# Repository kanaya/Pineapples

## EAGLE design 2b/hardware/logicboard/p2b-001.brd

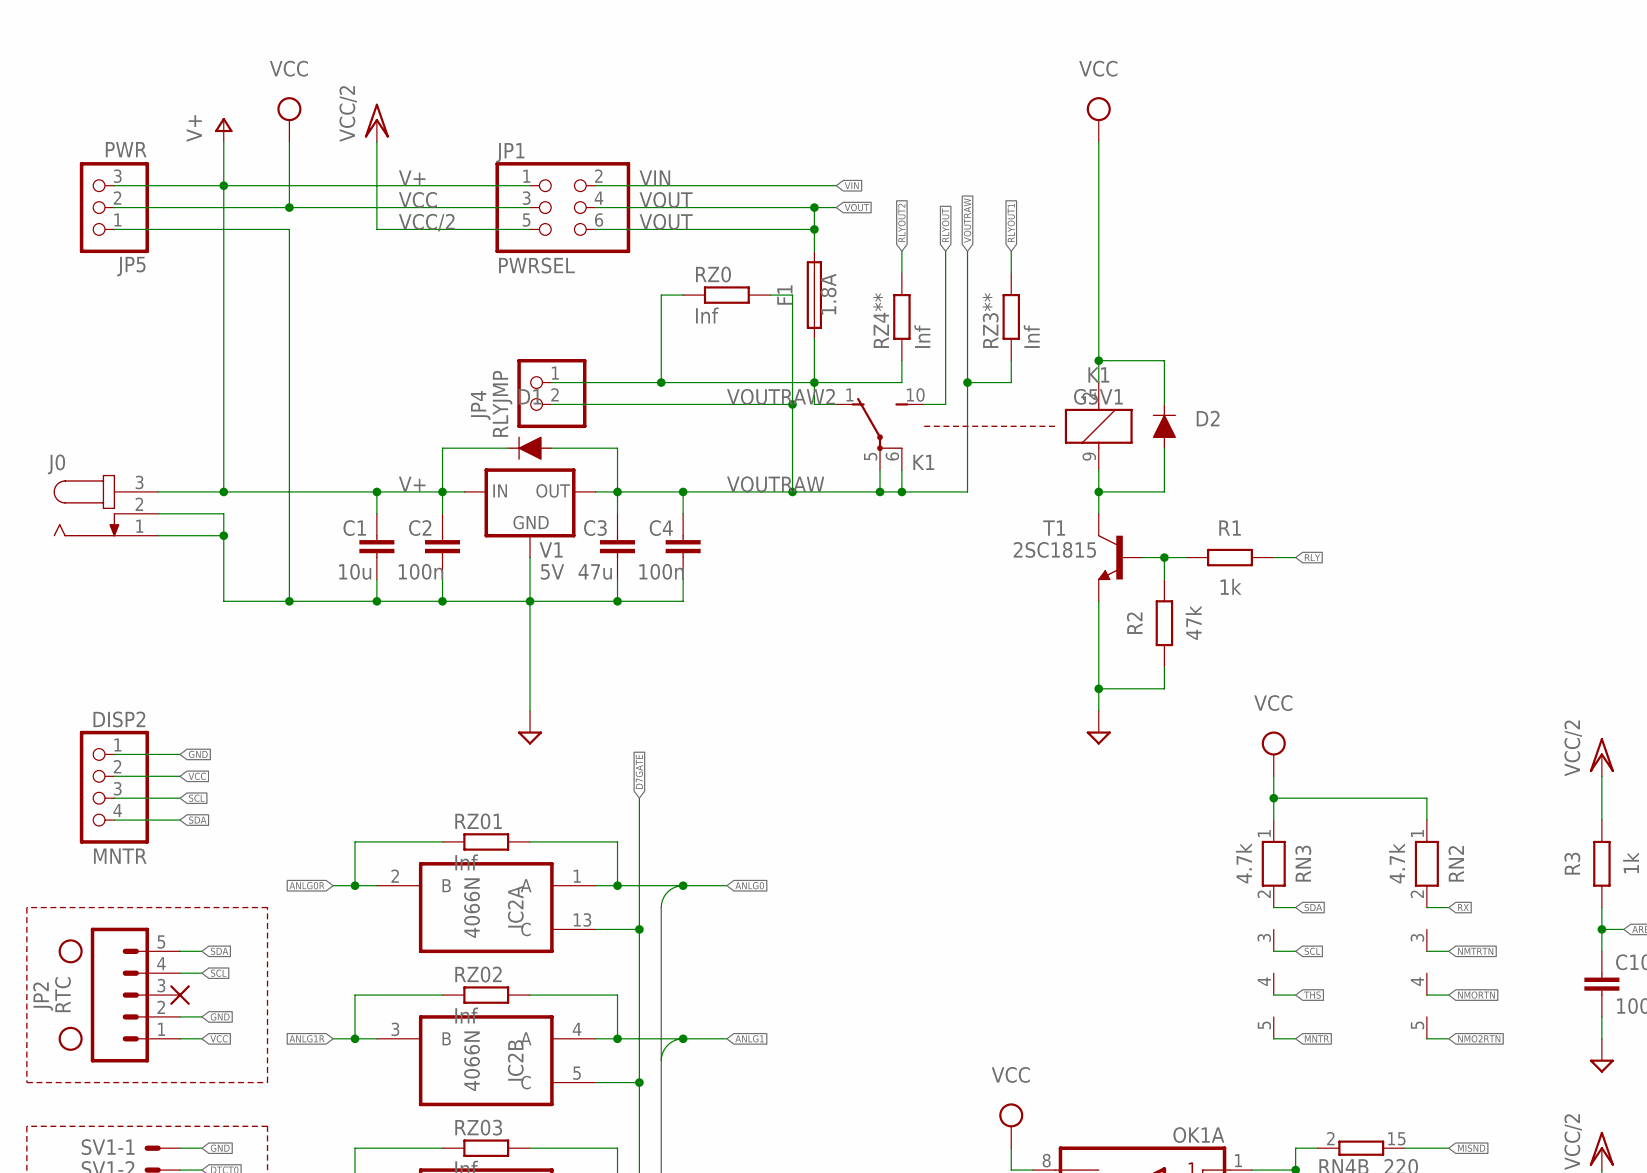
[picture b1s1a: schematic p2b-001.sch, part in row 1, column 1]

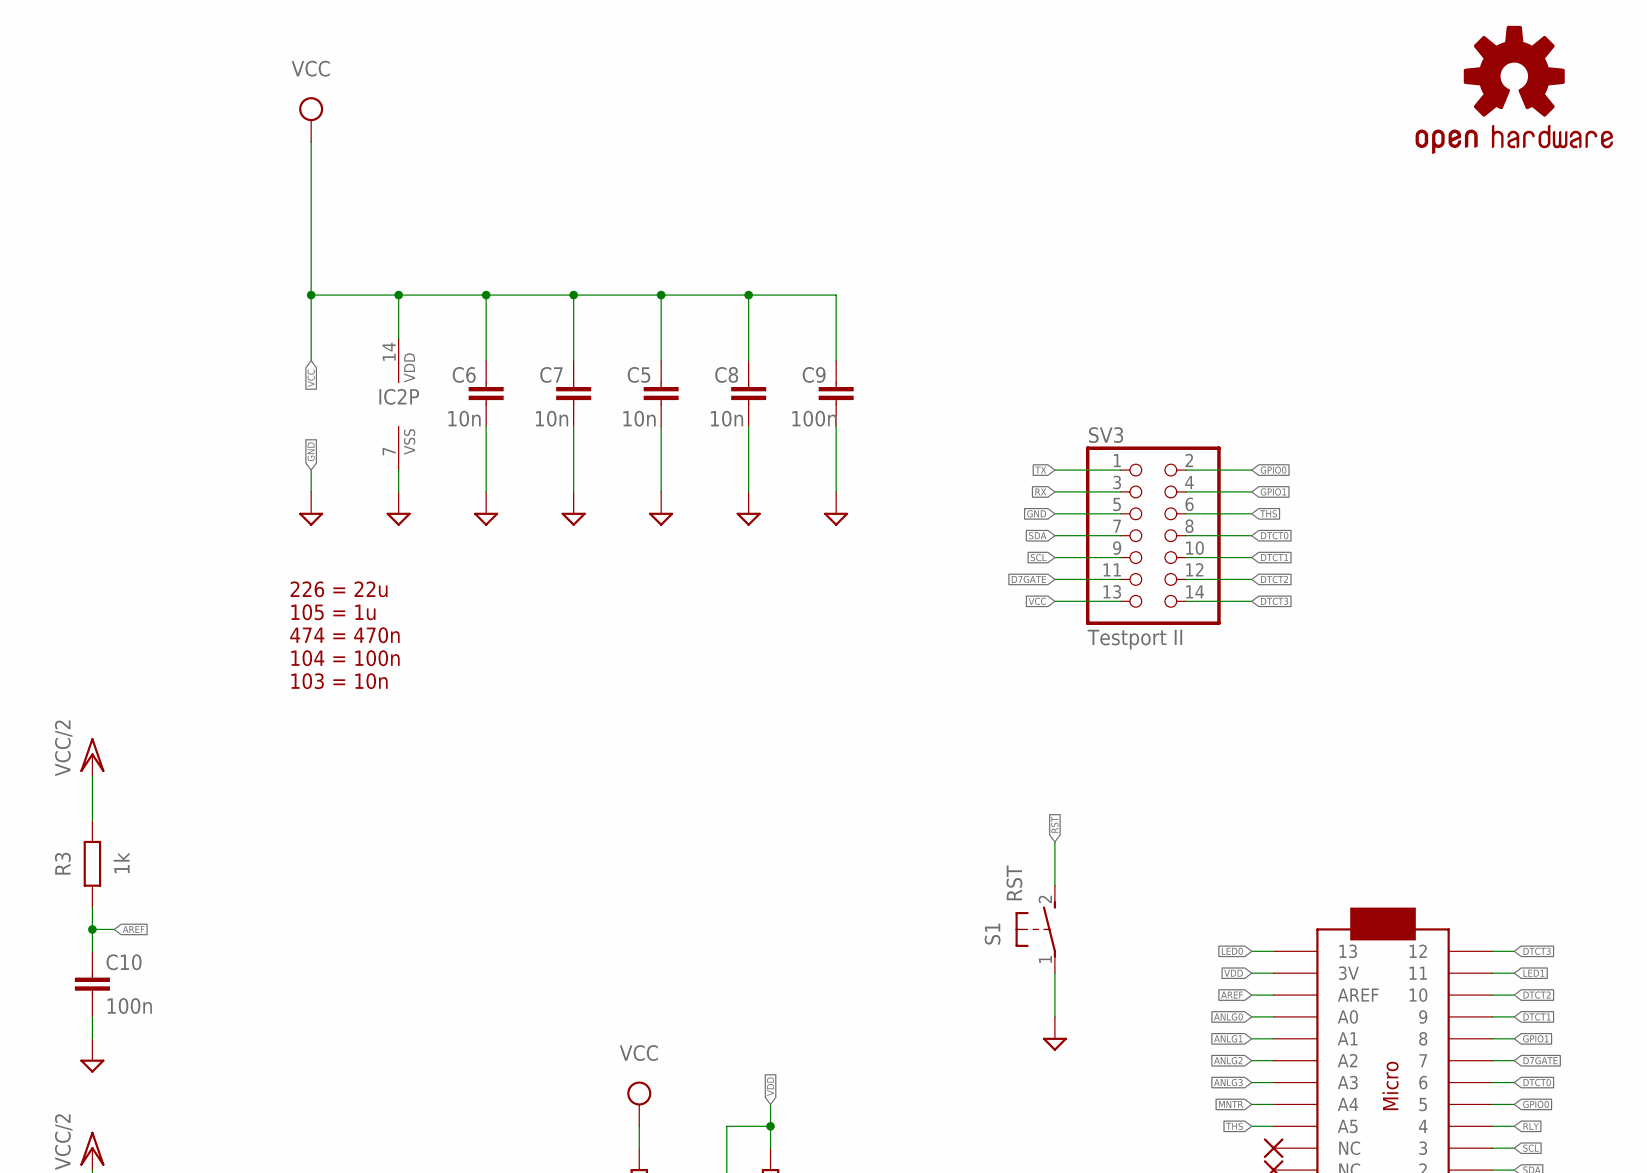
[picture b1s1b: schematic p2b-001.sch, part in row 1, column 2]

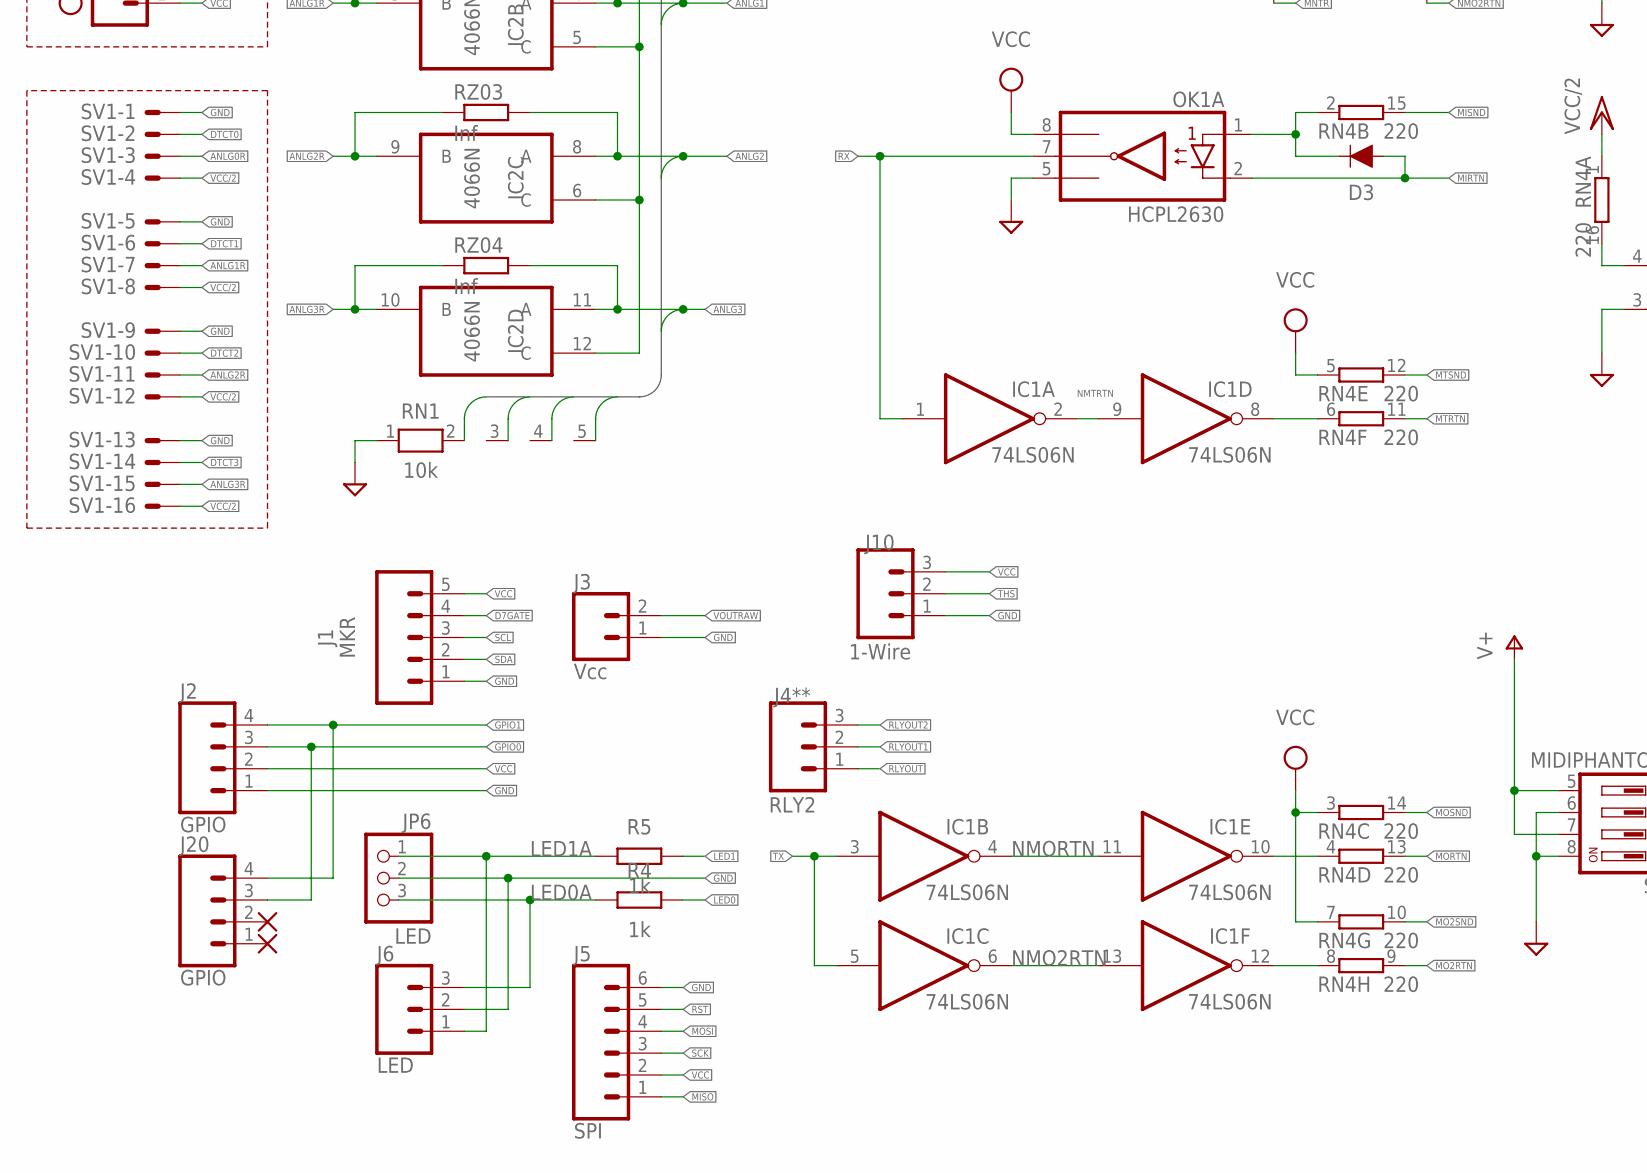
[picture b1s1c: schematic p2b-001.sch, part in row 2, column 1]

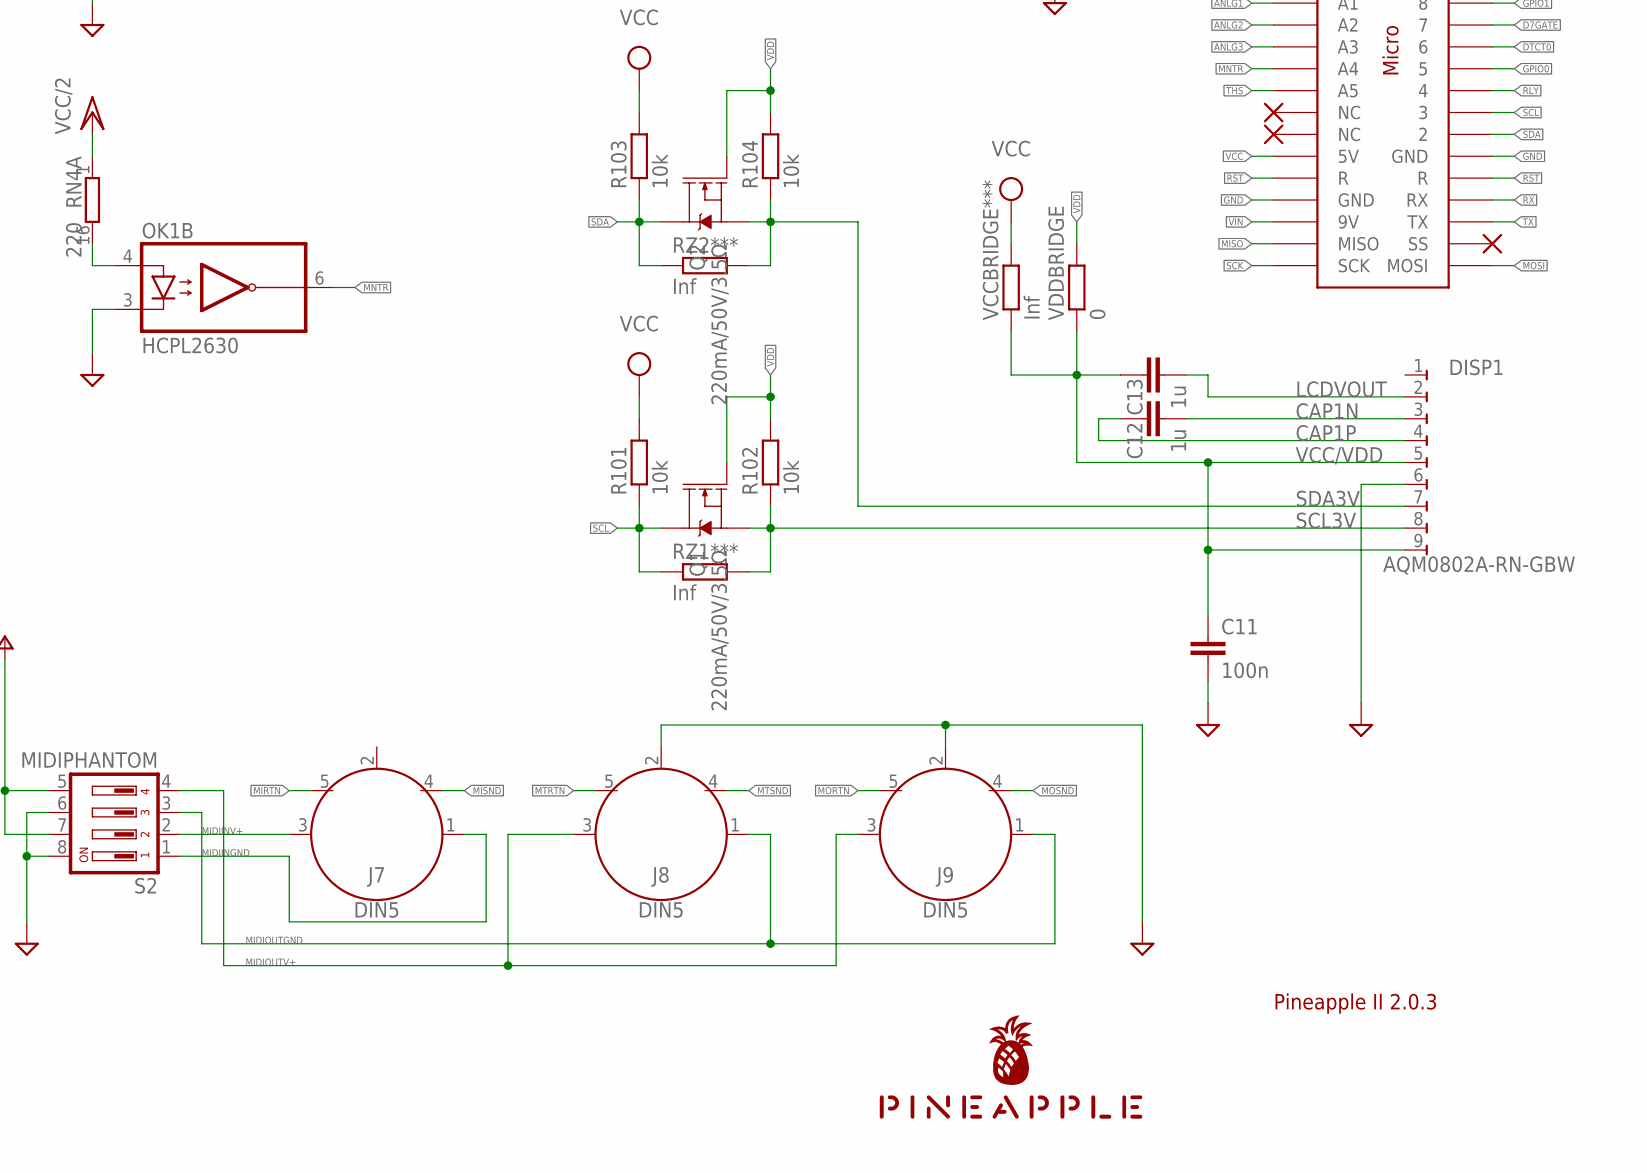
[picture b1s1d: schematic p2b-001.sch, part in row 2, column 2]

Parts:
C1: 10u; C025-030X050
C2, C4, C9, C10, C11: 100n; C025-024X044
C3: 47u; C025-050X050
C5, C6, C7, C8: 10n; C025-024X044
C12, C13: 1u; C050-024X044
D1, D2, D3: DIODE-1N4148
DISP1: AQM0802A-RN-GBW; AQM0802A-RN-GBW-FOOTPRINT
DISP2: MNTR; 1X04
F1: 1.8A; TE5
H1, H2: STAND-OFF
IC1: 74LS06N; DIL14
IC2: 4066N; DIL14
J0: JACK-PLUG0; SPC4077
J1: MKR; JST-5-PTH
J2: GPIO; JST-4-PTH
J3: Vcc; JST-2-PTH
J4**: RLY2; JST-3-PTH-NS
J5: SPI; 1X06_1.27MM
J6: LED; JST-3-PTH-VERT
J7, J8, J9: DIN5; DIN5-RA-PTH
J10: 1-Wire; JST-3-PTH-VERT
J20: GPIO; 1X04_1.27MM
JP1: PWRSEL; 2X03
JP2: RTC; 1X05
JP4: RLYJMP; 1X02
JP5: PWR; 1X03
JP6: LED; 1X03
K1: G5V1
LOGO1: OSHW-LOGOS-COPPER; OSHW-LOGO-S_COPPER
MC1: ARDUINOMICRO
OK1: HCPL2630; DIL08
Q1, Q2: 220mA/50V/3.5Ω; SOT23-3
R1, R3, R4, R5: 1k; 0204/5
R2: 47k; 0204/5
R101, R102, R103, R104: 10k; M2012
RN1: 10k; RN-5
RN2, RN3: 4.7k; RN-5
RN4: 220; DIL16
RZ0, RZ01, RZ1***, RZ02, RZ2***, RZ03, RZ3**, RZ04, RZ4**: Inf; M2012
S1: RST; B3F-31XX
S2: MIDIPHANTOM; DIP04YL
SV1: ML16LE; ML16L
SV3: Testport II; 2X07
T1: 2SC1815; TO92-ECB
U$1: PINEAPPLE450_SILK
V1: 5V; 78XXS
VCCBRIDGE***: Inf; M2012
VDDBRIDGE: 0; M2012

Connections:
ANLG0: IC2.1 (A), MC1.P$31 (A0), RN1.2, RZ01.2
ANLG0R: IC2.2 (B), RZ01.1, SV1.3
ANLG1: IC2.4 (A), MC1.P$30 (A1), RN1.3, RZ02.2
ANLG1R: IC2.3 (B), RZ02.1, SV1.7
ANLG2: IC2.8 (A), MC1.P$29 (A2), RN1.4, RZ03.2
ANLG2R: IC2.9 (B), RZ03.1, SV1.11
ANLG3: IC2.11 (A), MC1.P$28 (A3), RN1.5, RZ04.2
ANLG3R: IC2.10 (B), RZ04.1, SV1.15
AREF: C10.1, MC1.P$32 (AREF), R3.1
CAP1N: C12.2, DISP1.3
CAP1P: C12.1, DISP1.4
D7GATE: IC2.5 (C), IC2.6 (C), IC2.12 (C), IC2.13 (C), J1.4, MC1.P$6 (7), SV3.11
DTCT0: MC1.P$7 (6), SV1.2, SV3.8
DTCT1: MC1.P$4 (9), SV1.6, SV3.10
DTCT2: MC1.P$3 (10), SV1.10, SV3.12
DTCT3: MC1.P$1 (12), SV1.14, SV3.14
GND: C1.2, C2.2, C3.2, C4.2, C5.2, C6.2, C7.2, C8.2, C9.2, C10.2, C11.2, DISP1.6, DISP2.1, IC1.7 (GND), IC2.7 (VSS), J0.1, J0.2, J1.1, J2.1, J3.1, J5.6, J6.2, J8.2, J9.2, J10.1, JP2.2, JP5.1, JP6.2, MC1.P$12 (GND), MC1.P$21 (GND), OK1.3 (C2), OK1.5 (GND), R2.1, RN1.1, S1.1, S2.6, S2.8, SV1.1, SV1.5, SV1.9, SV1.13, SV3.5, T1.E, V1.GND
GPIO0: J2.3, J20.3, MC1.P$8 (5), SV3.2
GPIO1: J2.4, J20.4, MC1.P$5 (8), SV3.4
LCDVOUT: C13.2, DISP1.2
LED0: MC1.P$34 (13), R4.2
LED0A: J6.3, JP6.3, R4.1
LED1: MC1.P$2 (11), R5.2
LED1A: J6.1, JP6.1, R5.1
MIDIINGND: J7.1, S2.1
MIDIINSND: D3.C, OK1.1 (A1), RN4.2 (1)
MIDIINV+: J7.3, S2.2
MIDIOUTGND: J8.1, J9.1, S2.3
MIDIOUTV+: J8.3, J9.3, S2.4
MIRTN: D3.A, J7.5, OK1.2 (C1)
MISND: J7.4, RN4.15 (2)
MISO: J5.1, MC1.P$19 (MISO)
MNTR: MC1.P$27 (A4), OK1.6 (VO2), RN3.5
MNTRA: OK1.4 (A2), RN4.16 (2)
MO2RTN: RN4.9 (2)
MO2RTNRAW: IC1.12 (O), RN4.8 (1)
MO2SND: RN4.10 (2)
MORTN: J9.5, RN4.13 (2)
MORTNRAW: IC1.10 (O), RN4.4 (1)
MOSI: J5.4, MC1.P$17 (MOSI)
MOSND: J9.4, RN4.14 (2)
MTRTN: J8.5, RN4.11 (2)
MTRTNRAW: IC1.8 (O), RN4.6 (1)
MTSND: J8.4, RN4.12 (2)
NMO2RTN: IC1.6 (O), IC1.13 (I), RN2.5
NMORTN: IC1.4 (O), IC1.11 (I), RN2.4
NMTRTN: IC1.2 (O), IC1.9 (I), RN2.3
RLY: MC1.P$9 (4), R1.2
RLYDRV: R1.1, R2.2, T1.B
RLYOUT: J4**.1, K1.10 (S)
RLYOUT1: J4**.2, RZ3**.2
RLYOUT2: J4**.3, RZ4**.2
RLYSNK: D2.A, K1.9 (2), T1.C
RST: J5.5, MC1.P$13 (R), MC1.P$22 (R), S1.2 (S)
RX: IC1.1 (I), MC1.P$14 (RX), OK1.7 (VO1), RN2.2, SV3.3
SCK: J5.3, MC1.P$18 (SCK)
SCL: DISP2.3, J1.3, JP2.4, MC1.P$10 (3), Q1.3 (D), R101.1, RN3.3, RZ1***.1, SV3.9
SCL3V: DISP1.8, Q1.2 (S), R102.1, RZ1***.2
SDA: DISP2.4, J1.2, JP2.5, MC1.P$11 (2), Q2.3 (D), R103.1, RN3.2, RZ2***.1, SV3.7
SDA3V: DISP1.7, Q2.2 (S), R104.1, RZ2***.2
THS: J10.2, MC1.P$26 (A5), RN3.4, SV3.6
TX: IC1.3 (I), IC1.5 (I), MC1.P$15 (TX), SV3.1
V+: C1.1, C2.1, D1.C, J0.3, JP1.1, JP5.3, S2.5, S2.7, V1.IN
VCC: C5.1, C6.1, C7.1, C8.1, C9.1, D2.C, DISP2.2, IC1.14 (VCC), IC2.14 (VDD), J1.5, J2.2, J5.2, J10.3, JP1.3, JP2.1, JP5.2, K1.2 (1), MC1.P$23 (5V), OK1.8 (VCC), R101.2, R103.2, RN2.1, RN3.1, RN4.3 (1), RN4.5 (1), RN4.7 (1), SV3.13, VCCBRIDGE***.2
VCC/2: JP1.5, R3.2, RN4.1, SV1.4, SV1.8, SV1.12, SV1.16
VCC/VDD: C11.1, C13.1, DISP1.5, DISP1.9, VCCBRIDGE***.1, VDDBRIDGE.1
VDD: MC1.P$33 (3V), Q1.1 (G), Q2.1 (G), R102.2, R104.2, VDDBRIDGE.2
VIN: JP1.2, MC1.P$20 (9V)
VOUT: F1.2, JP1.4, JP1.6
VOUTRAW: C3.1, C4.1, D1.A, J3.2, JP4.2, K1.5, K1.6, RZ0.2, RZ3**.1, V1.OUT
VOUTRAW2: F1.1, JP4.1, K1.1 (O), RZ0.1, RZ4**.1

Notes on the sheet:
Pineapple II 2.0.3
226 = 22u 105 = 1u 474 = 470n 104 = 100n 103 = 10n

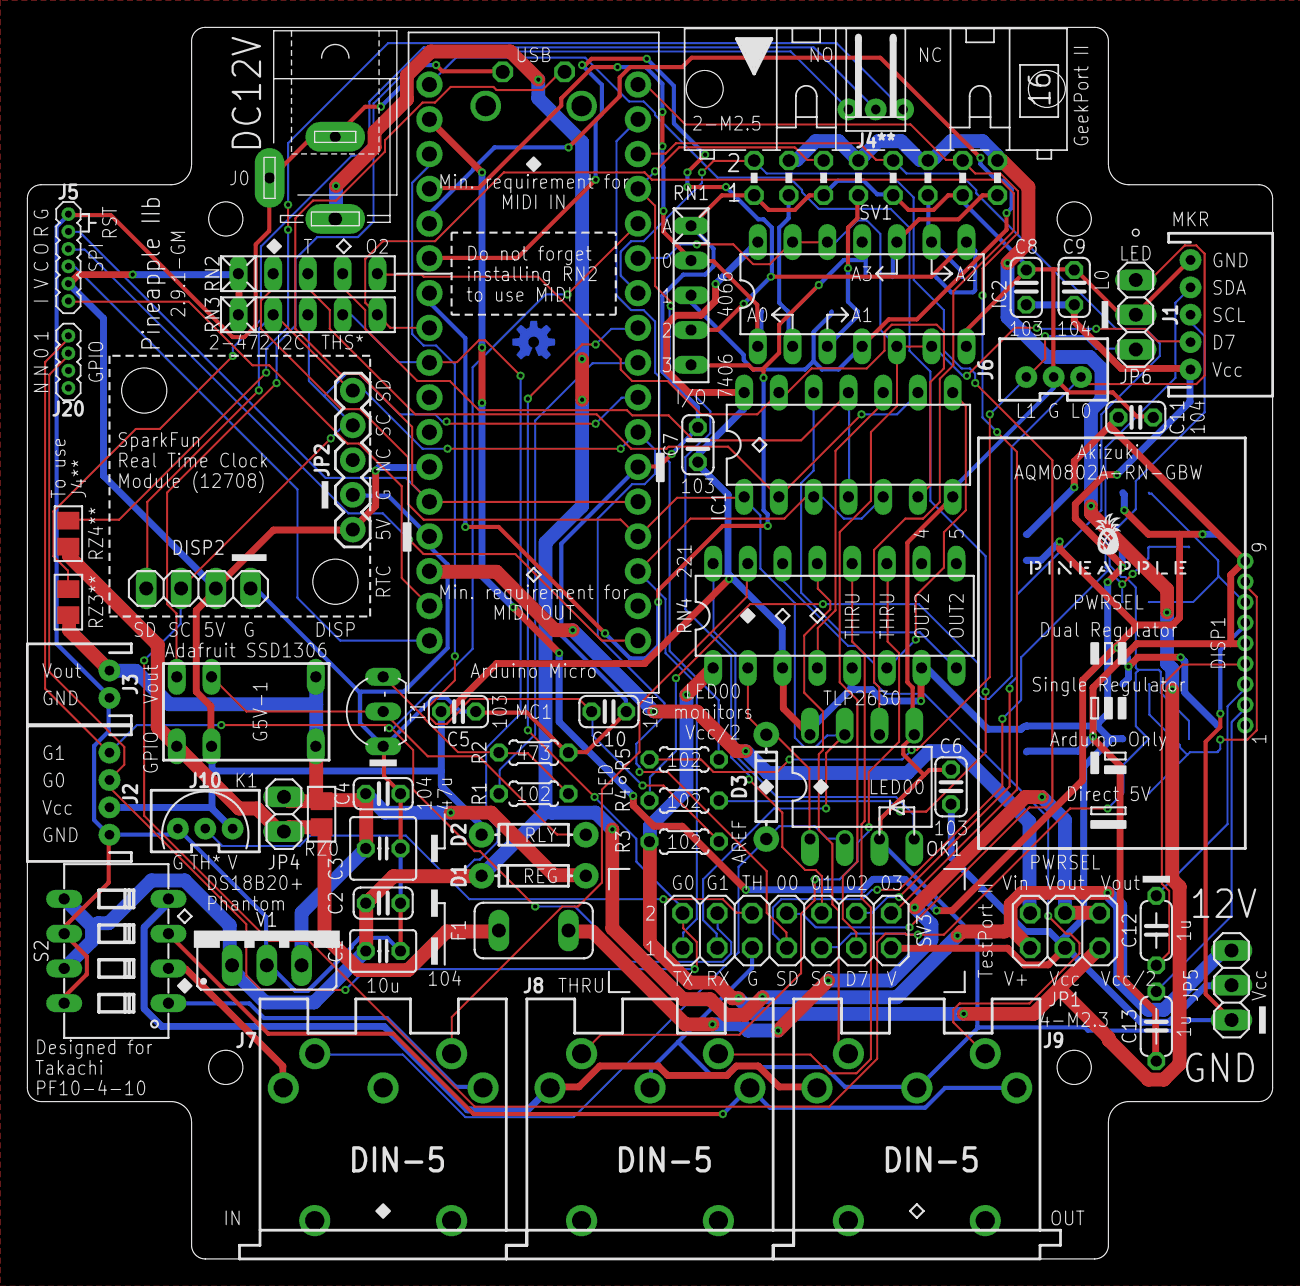
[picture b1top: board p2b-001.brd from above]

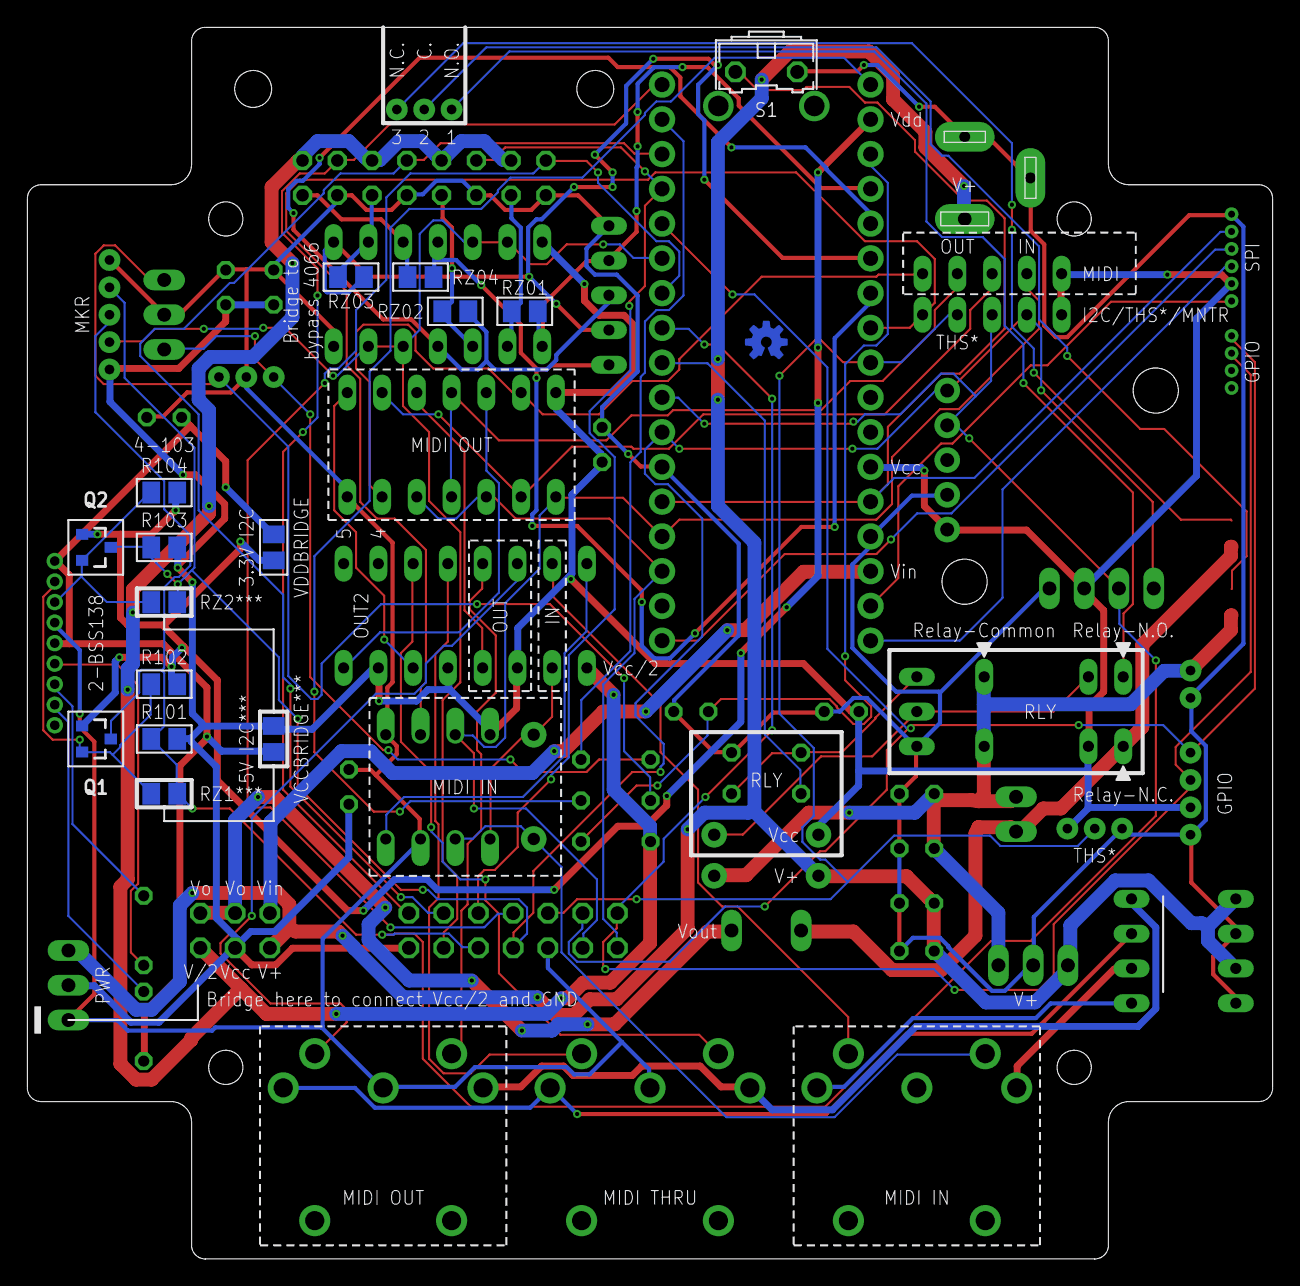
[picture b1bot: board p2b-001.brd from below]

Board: 2 copper layers, 91.0 x 90.0 mm, 77 parts (16 on the bottom side), 69 nets.

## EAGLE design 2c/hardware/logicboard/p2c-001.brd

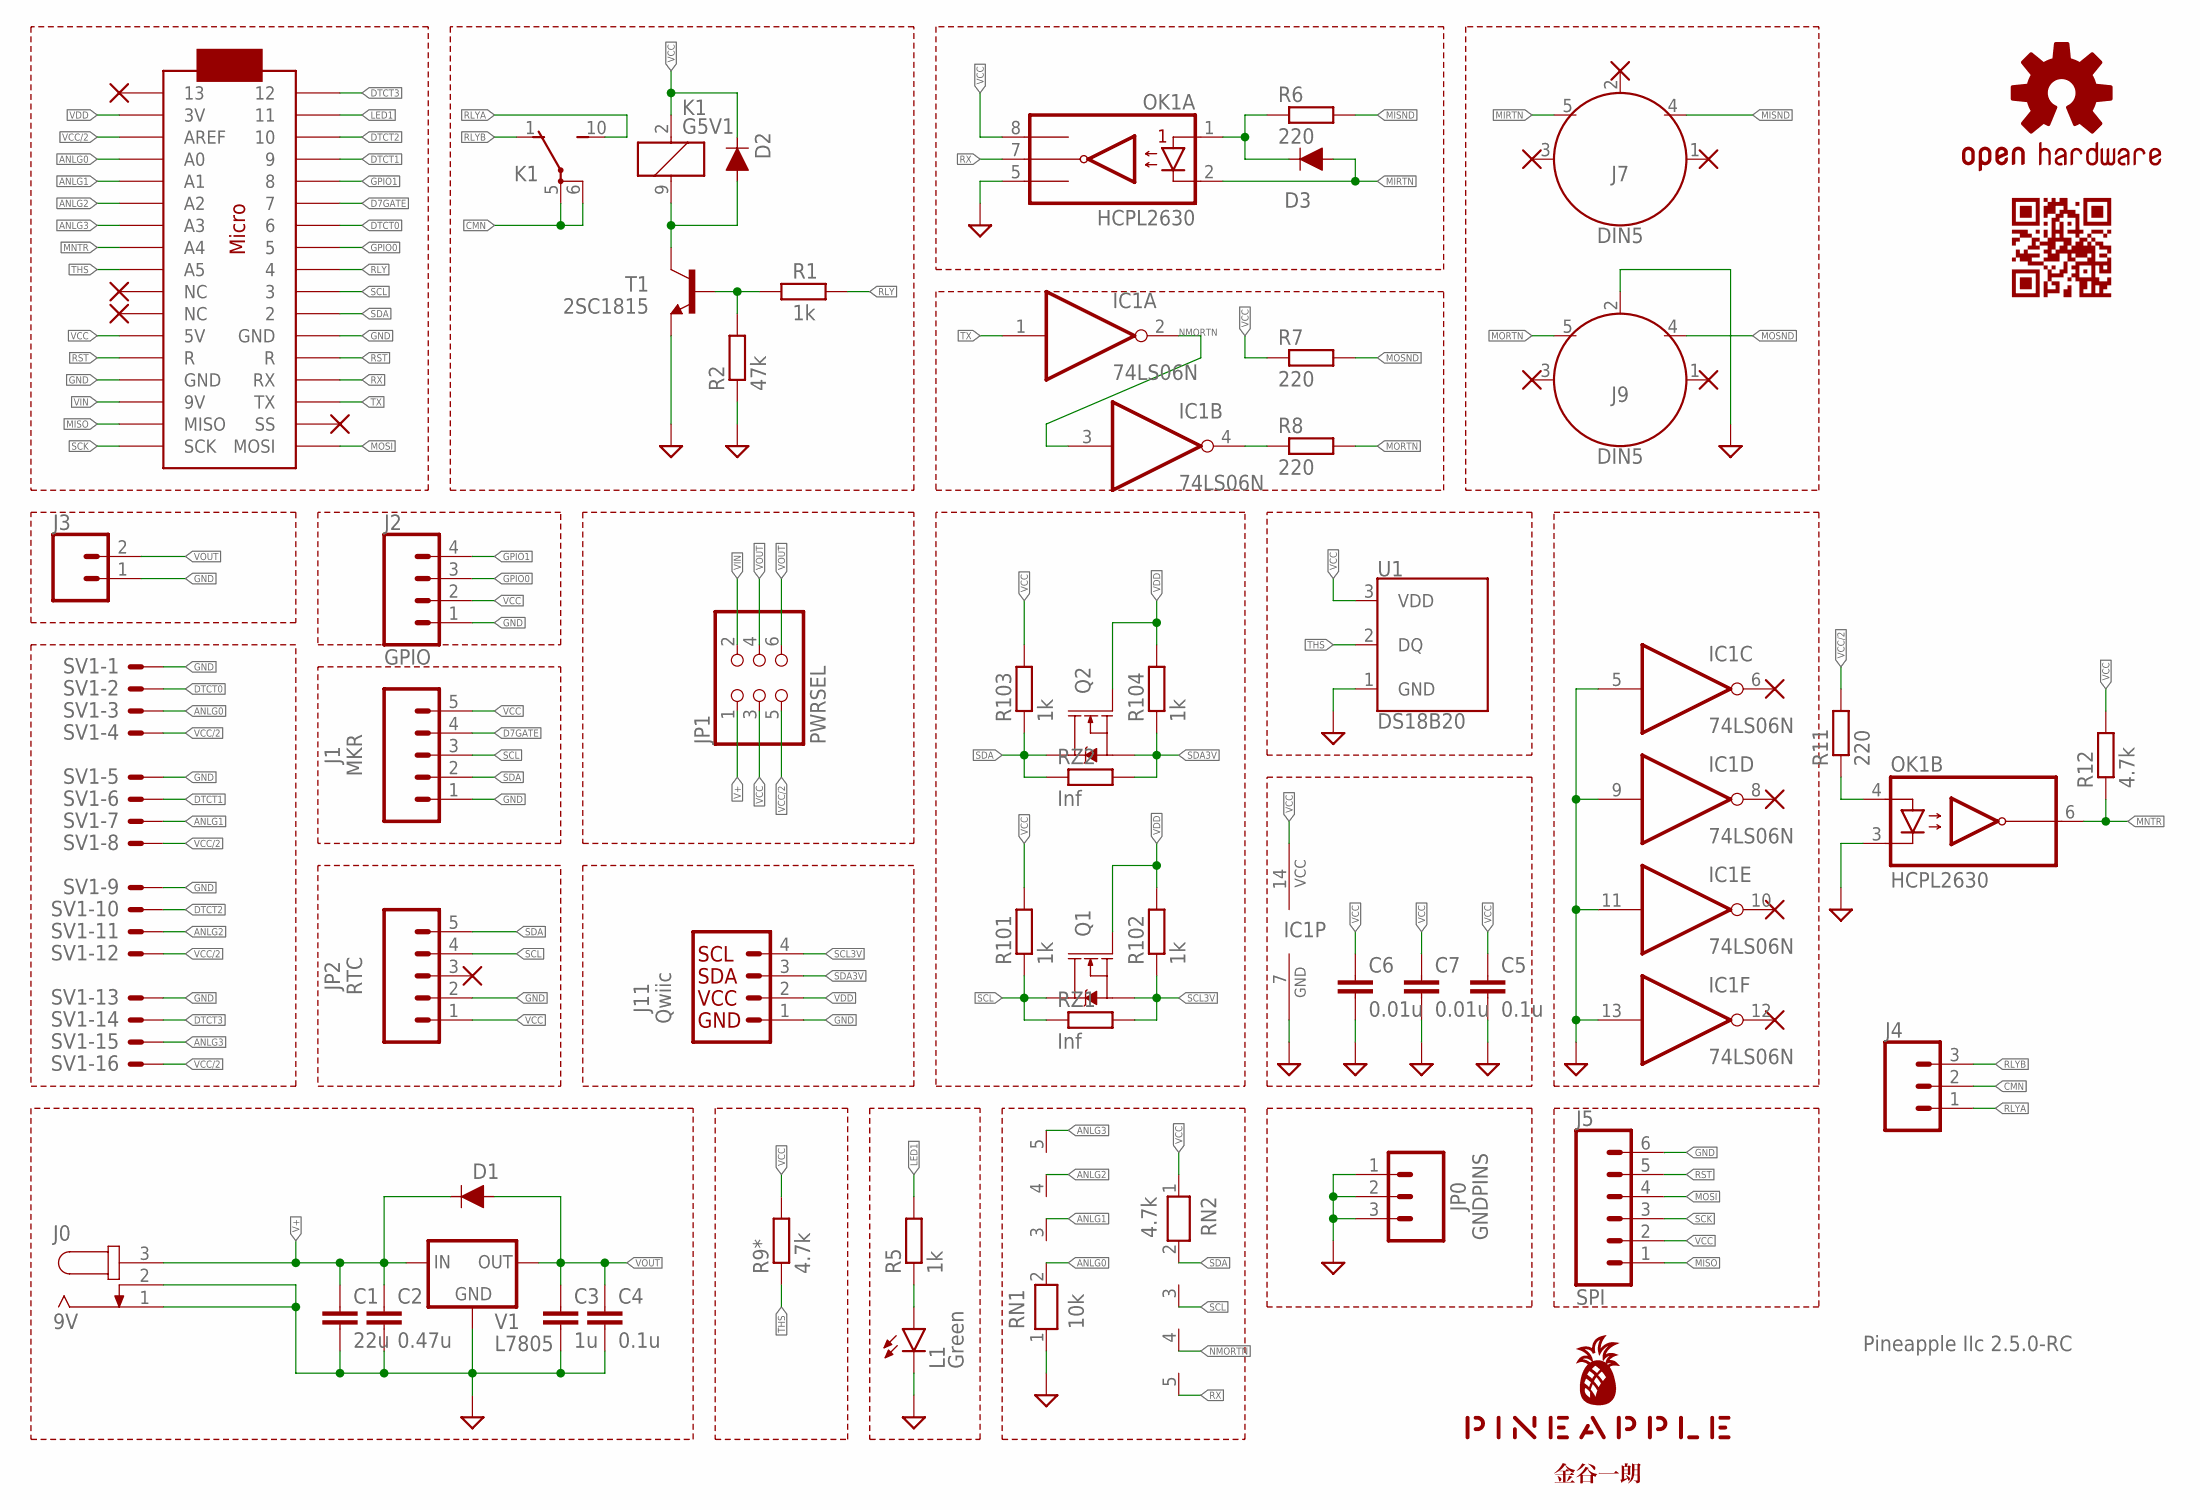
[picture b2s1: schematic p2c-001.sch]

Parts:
C1: 22u; C025-050X050
C2: 0.47u; C050-024X044
C3: 1u; C050-024X044
C4, C5: 0.1u; C025-024X044
C6, C7: 0.01u; C025-024X044
D1, D2, D3: DIODE-1N4148
IC1: 74LS06N; DIL14
J0: 9V; SPC4077
J1: MKR; JST-5-PTH
J2: GPIO; JST-4-PTH
J3: CONN_02JST-PTH-2; JST-2-PTH
J4: CONN_03JST-PTH-NS; JST-3-PTH-NS
J5: SPI; 1X06_1.27MM
J7, J9: DIN5; DIN5-RA-PTH
J11: Qwiic; 1X04_1MM_RA
JP0: GNDPINS; 1X03
JP1: PWRSEL; 2X03
JP2: RTC; 1X05
K1: G5V1
L1: Green; LED3MM
LOGO1: OSHW-LOGOS-COPPER; OSHW-LOGO-S_COPPER
OK1: HCPL2630; DIL08
Q1, Q2: 220mA/50V/3.5Ω; SOT23-3
R1, R5: 1k; 0204/5
R2: 47k; 0204/5
R6, R7, R8, R11: 220; 0204/5
R9*, R12: 4.7k; 0204/5
R101, R102, R103, R104: 1k; R2012
RN1: 10k; RN-5
RN2: 4.7k; RN-5
RZ1, RZ2: Inf; R2012
SV1: ML16LE; ML16L
T1: 2SC1815; TO92-ECB
U1: DS18B20; TO-92-AMMO
U$1: PINEAPPLE450_SILK
U$2: ARDUINOMICRO
U$3: KANAYA768_SILK
U$4: CARDQRCODE450_SILK
V1: L7805; 78XXS

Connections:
ANLG0: RN1.2, SV1.3, U$2.P$31 (A0)
ANLG1: RN1.3, SV1.7, U$2.P$30 (A1)
ANLG2: RN1.4, SV1.11, U$2.P$29 (A2)
ANLG3: RN1.5, SV1.15, U$2.P$28 (A3)
CMN: J4.2, K1.5, K1.6
D7GATE: J1.4, U$2.P$6 (7)
DTCT0: SV1.2, U$2.P$7 (6)
DTCT1: SV1.6, U$2.P$4 (9)
DTCT2: SV1.10, U$2.P$3 (10)
DTCT3: SV1.14, U$2.P$1 (12)
GND: C1.2, C2.2, C3.2, C4.2, C5.2, C6.2, C7.2, IC1.5 (I), IC1.7 (GND), IC1.9 (I), IC1.11 (I), IC1.13 (I), J0.1, J0.2, J1.1, J2.1, J3.1, J5.6, J9.2, J11.1 (GND), JP0.1, JP0.2, JP0.3, JP2.2, L1.K (C), OK1.3 (C2), OK1.5 (GND), R2.1, RN1.1, SV1.1, SV1.5, SV1.9, SV1.13, T1.E, U1.1 (GND), U$2.P$12 (GND), U$2.P$21 (GND), V1.GND
GPIO0: J2.3, U$2.P$8 (5)
GPIO1: J2.4, U$2.P$5 (8)
LED1: R5.2, U$2.P$2 (11)
LED1A: L1.A, R5.1
MIA: D3.C, OK1.1 (A1), R6.1
MIRTN: D3.A, J7.5, OK1.2 (C1)
MISND: J7.4, R6.2
MISO: J5.1, U$2.P$19 (MISO)
MNTR: OK1.6 (VO2), R12.1, U$2.P$27 (A4)
MNTRA: OK1.4 (A2), R11.1
MORTN: J9.5, R8.2
MORTNRAW: IC1.4 (O), R8.1
MOSI: J5.4, U$2.P$17 (MOSI)
MOSND: J9.4, R7.2
NMORTN: IC1.2 (O), IC1.3 (I), RN2.4
RLY: R1.2, U$2.P$9 (4)
RLYA: J4.1, K1.10 (S)
RLYB: J4.3, K1.1 (O)
RLYC: D2.A, K1.9 (2), T1.C
RLYQ: R1.1, R2.2, T1.B
RST: J5.5, U$2.P$13 (R), U$2.P$22 (R)
RX: OK1.7 (VO1), RN2.5, U$2.P$14 (RX)
SCK: J5.3, U$2.P$18 (SCK)
SCL: J1.3, JP2.4, Q1.3 (D), R101.1, RN2.3, RZ1.1, U$2.P$10 (3)
SCL3V: J11.4 (SCL), Q1.2 (S), R102.1, RZ1.2
SDA: J1.2, JP2.5, Q2.3 (D), R103.1, RN2.2, RZ2.1, U$2.P$11 (2)
SDA3V: J11.3 (SDA), Q2.2 (S), R104.1, RZ2.2
THS: R9*.1, U1.2 (DQ), U$2.P$26 (A5)
TX: IC1.1 (I), U$2.P$15 (TX)
V+: C1.1, C2.1, D1.C, J0.3, JP1.1, V1.IN
VCC: C5.1, C6.1, C7.1, D2.C, IC1.14 (VCC), J1.5, J2.2, J5.2, JP1.3, JP2.1, K1.2 (1), OK1.8 (VCC), R7.1, R9*.2, R12.2, R101.2, R103.2, RN2.1, U1.3 (VDD), U$2.P$23 (5V)
VCC/2: JP1.5, R11.2, SV1.4, SV1.8, SV1.12, SV1.16, U$2.P$32 (AREF)
VDD: J11.2 (VCC), Q1.1 (G), Q2.1 (G), R102.2, R104.2, U$2.P$33 (3V)
VIN: JP1.2, U$2.P$20 (9V)
VOUT: C3.1, C4.1, D1.A, J3.2, JP1.4, JP1.6, V1.OUT

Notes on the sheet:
Pineapple IIc 2.5.0-RC

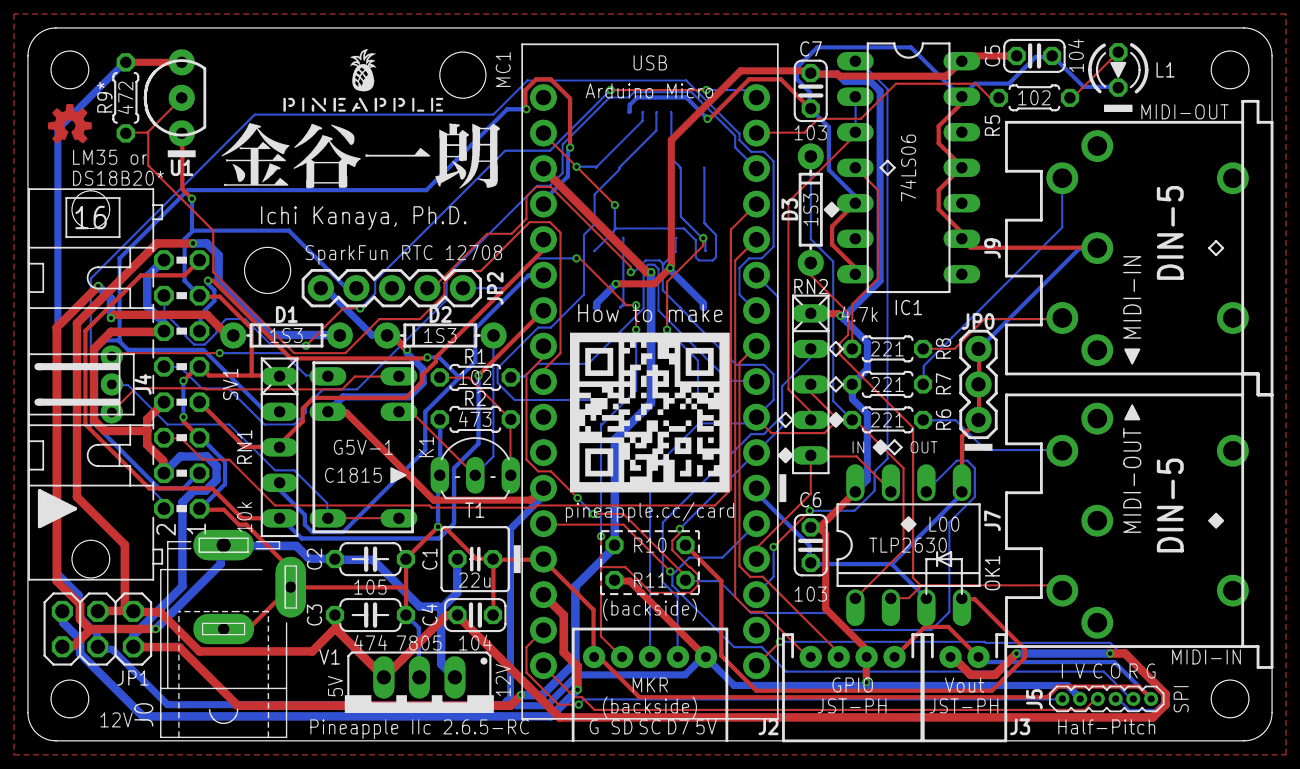
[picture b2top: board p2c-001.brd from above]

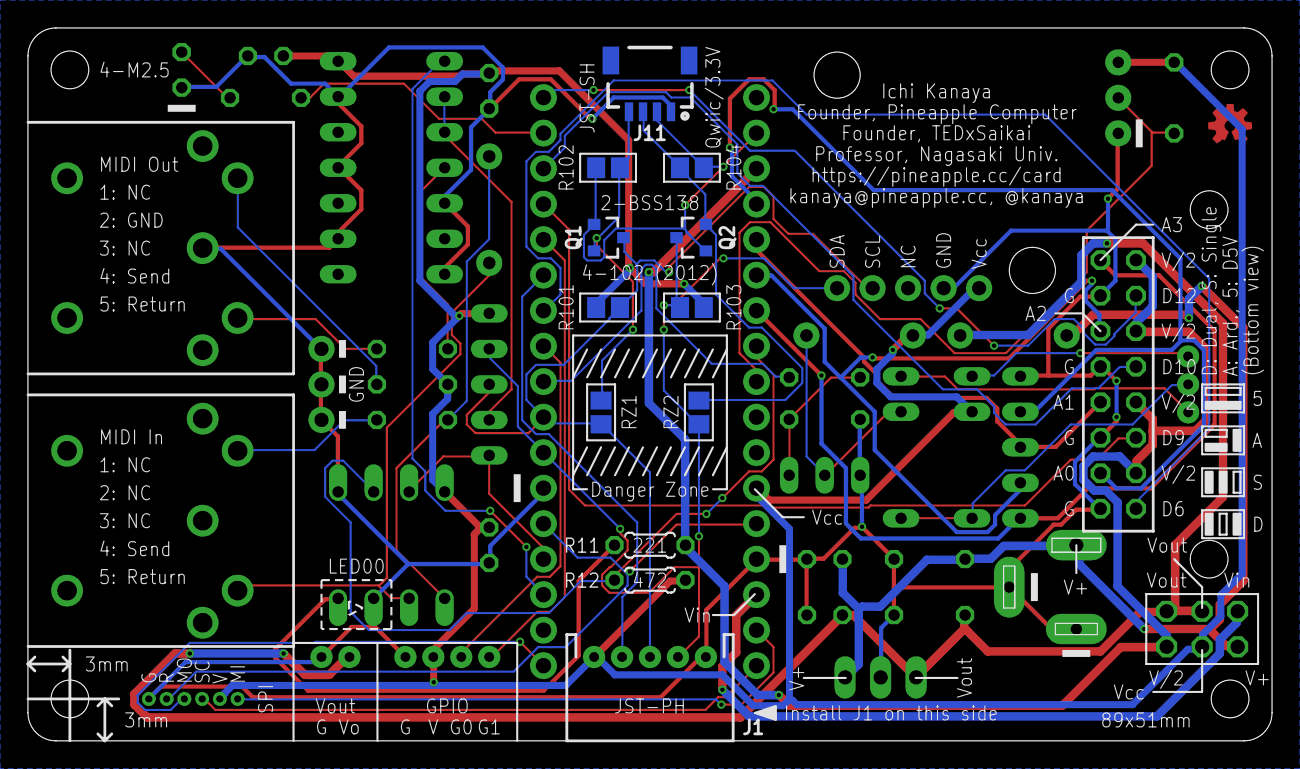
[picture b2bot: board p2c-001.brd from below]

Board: 2 copper layers, 89.0 x 51.0 mm, 56 parts (12 on the bottom side), 46 nets.

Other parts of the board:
U$5, U$6: STAND-OFF

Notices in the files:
parts and their libraries:
SparkFun-DiscreteSemi: Licensing: Creative Commons ShareAlike 4.0 International - https://creativecommons.org/licenses/by-sa/4.0
